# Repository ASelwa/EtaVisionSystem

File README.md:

**EtaVisionSystem**
===============

This repo contains code and documentation for AeroVelo's Eta speedbike vision system.

It includes code for the Arduino Mega, code for the minimOSD, and some documentation as well as datasheets.

####BRANCHES

The _master_ branch contains the most recent updates.

The _BM-2014_ branch is a quick way to access the code ran at Battle Mountain in September 2014. There were several bugs and issues to be addressed, however it still used at road testing several times leading up to 2015.

The _No-Serial-Printing_ branch contains the code ran at Battle Mountain 2014 without serial printing.

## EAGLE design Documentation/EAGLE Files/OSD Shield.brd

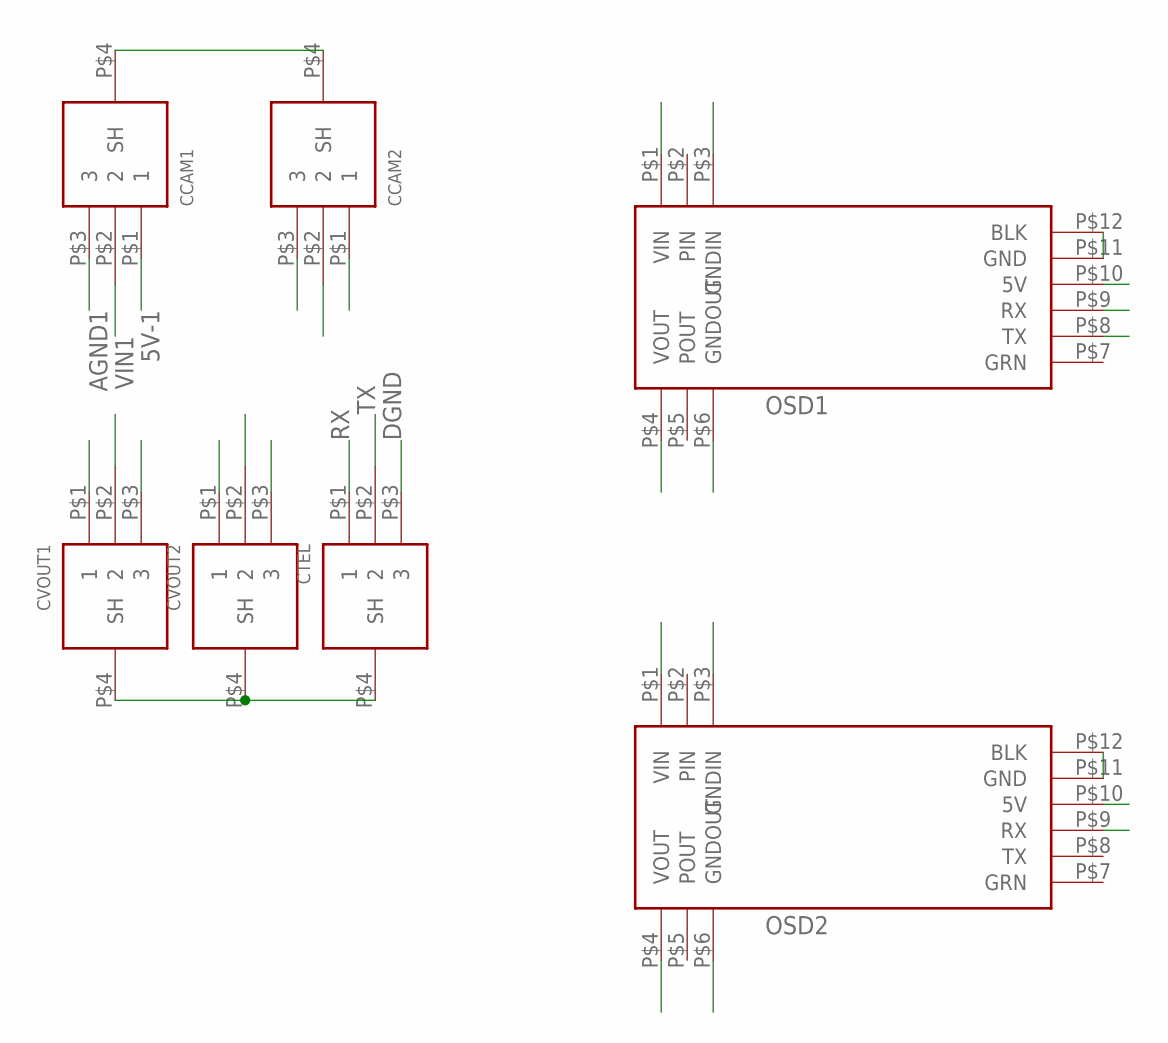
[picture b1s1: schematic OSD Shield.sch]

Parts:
CCAM1, CCAM2: TRA3M
CTEL: TRA3MBARE; TRA3M-BARE
CVOUT1, CVOUT2: TRA3MBARE; TRA3M-BARE
OSD1, OSD2: MINIM-OSD

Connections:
5V-1: CCAM1.P$1 (1), CVOUT1.P$1 (1), OSD1.P$10 (5V)
5V-2: CCAM2.P$1 (1), CVOUT2.P$1 (1), OSD2.P$10 (5V)
AGND1: CCAM1.P$3 (3), CVOUT1.P$3 (3), OSD1.P$3 (GNDIN), OSD1.P$6 (GNDOUT)
AGND2: CCAM2.P$3 (3), CVOUT2.P$3 (3), OSD2.P$3 (GNDIN), OSD2.P$6 (GNDOUT)
DGND: CTEL.P$3 (3), OSD1.P$11 (GND), OSD1.P$12 (BLK), OSD2.P$11 (GND), OSD2.P$12 (BLK)
RX: CTEL.P$1 (1), OSD1.P$9 (RX), OSD2.P$9 (RX)
SHLD: CCAM1.P$4 (SH), CCAM2.P$4 (SH), CTEL.P$4 (SH), CVOUT1.P$4 (SH), CVOUT2.P$4 (SH)
TX: CTEL.P$2 (2), OSD1.P$8 (TX)
VIN1: CCAM1.P$2 (2), OSD1.P$1 (VIN)
VIN2: CCAM2.P$2 (2), OSD2.P$1 (VIN)
VOUT1: CVOUT1.P$2 (2), OSD1.P$4 (VOUT)
VOUT2: CVOUT2.P$2 (2), OSD2.P$4 (VOUT)

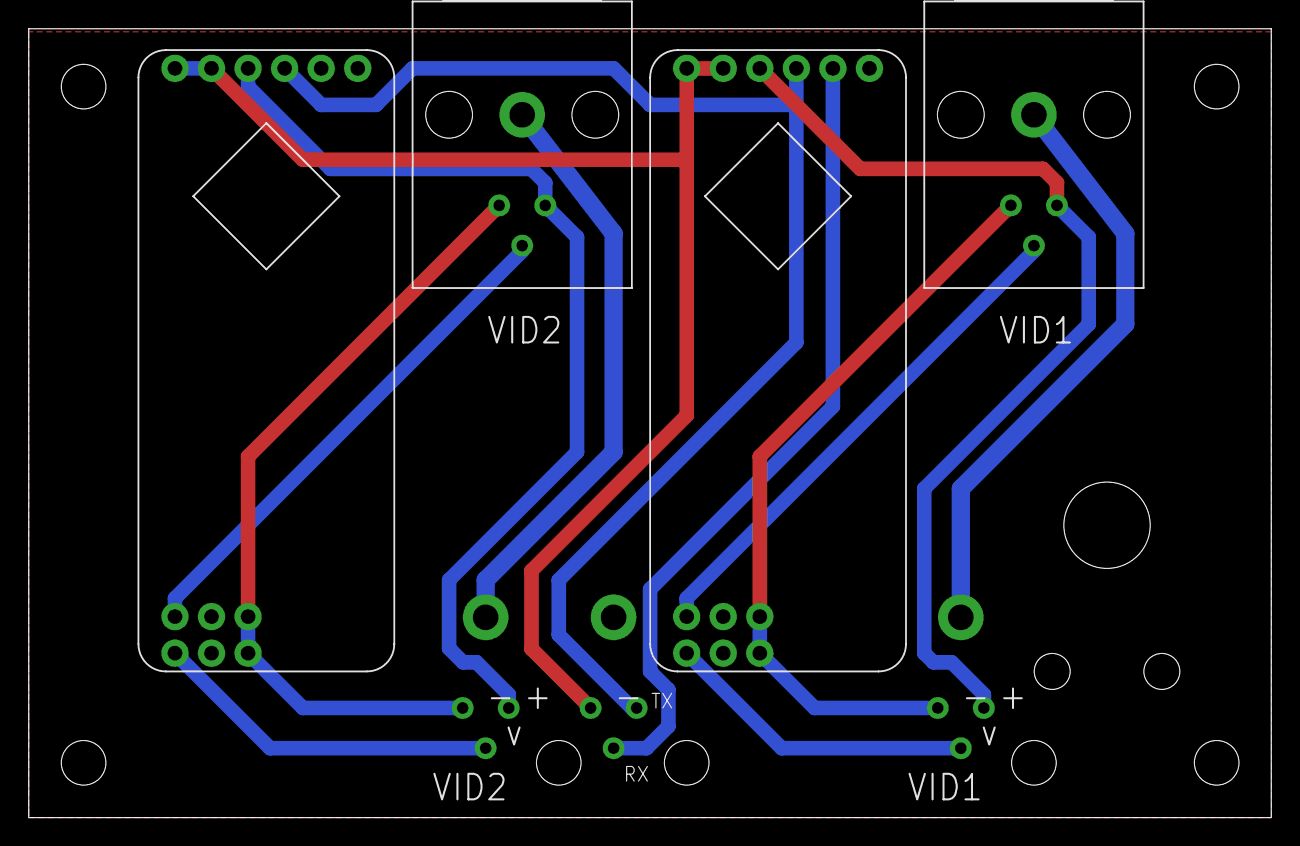
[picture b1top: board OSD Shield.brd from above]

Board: 2 copper layers, 86.3 x 54.8 mm, 7 parts (0 on the bottom side), 12 nets.

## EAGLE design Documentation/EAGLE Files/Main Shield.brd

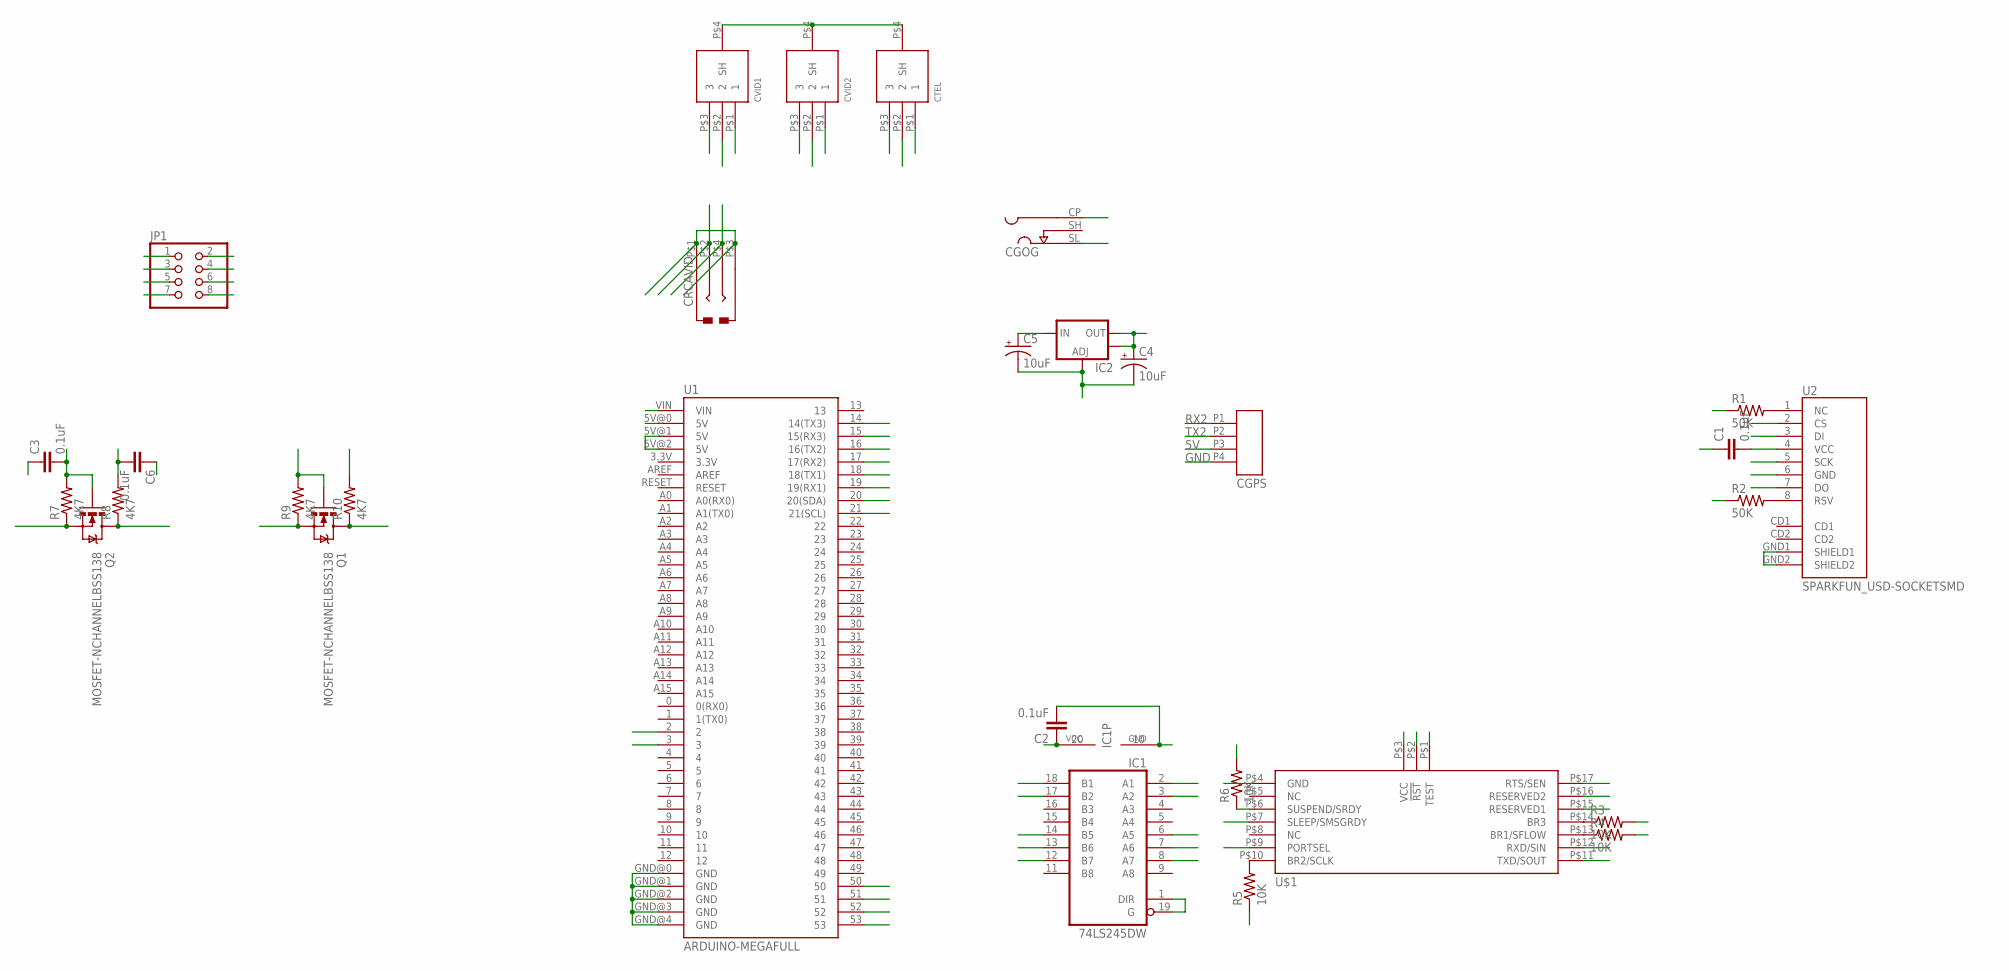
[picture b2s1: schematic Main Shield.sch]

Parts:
C1, C2, C3, C6: 0.1uF; 0603-CAP
C4, C5: 10uF; EIA3216
CGOG: L722RAS
CGPS: TRAPC4MSX
CRCAVID: RCJ-2123
CTEL: TRA3M
CVID1, CVID2: TRA3M
IC1: 74LS245DW; SO20W
IC2: V_REG_LM1117SOT223; SOT223
JP1: PINHD-2X04_MICROMATCH; MICROMATCH-8
Q1, Q2: MOSFET-NCHANNELBSS138; SOT23
R1, R2: 50K; 0603-RES
R3, R4, R5, R6: 10K; 0603-RES
R7, R8, R9, R10: 4K7; 0603-RES
U1: ARDUINO-MEGAFULL; ARDUINO_MEGA
U2: SPARKFUN_USD-SOCKETSMD; SPARKFUN_MICRO-SD-SOCKET-PP
U$1: ANTAP281MXIB

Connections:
3V3: C1.2, C2.1, C3.2, C4.A (+), IC1.20 (VCC), IC2.2 (OUT), IC2.4 (OUT), JP1.2, Q1.1 (G), Q2.1 (G), R1.1, R2.1, R3.2, R4.2, R5.1, R6.2, R7.2, R9.2, U2.4 (VCC), U$1.P$3 (VCC)
5V: C5.A (+), C6.2, CGPS.P3, CVID1.P$1 (1), CVID2.P$1 (1), IC2.3 (IN), JP1.4, R8.2, R10.2, U1.5V@0 (5V), U1.5V@1 (5V), U1.5V@2 (5V)
!RST!ANT: IC1.3 (A2), U$1.P$2 (!RST!)
!RST!ANT5V: IC1.17 (B2), U1.3
CSMMC: IC1.8 (A7), U2.2 (CS)
DIMMC: IC1.7 (A6), U2.3 (DI)
DOMMC: U1.50, U2.7 (DO)
GND: C1.1, C2.2, C3.1, C4.C (-), C5.C (-), C6.1, CGOG.SL (SLEEVE), CGPS.P4, CRCAVID.P$1, CRCAVID.P$3, CTEL.P$3 (3), CTEL.P$4 (SH), CVID1.P$3 (3), CVID1.P$4 (SH), CVID2.P$3 (3), CVID2.P$4 (SH), IC1.1 (DIR), IC1.10 (GND), IC1.19 (G), IC2.1 (ADJ), JP1.1, JP1.3, U1.GND@0 (GND), U1.GND@1 (GND), U1.GND@2 (GND), U1.GND@3 (GND), U1.GND@4 (GND), U2.6 (GND), U2.GND1 (SHIELD1), U2.GND2 (SHIELD2), U$1.P$1 (TEST), U$1.P$4 (GND), U$1.P$7 (SLEEP/SMSGRDY), U$1.P$9 (PORTSEL), U$1.P$15 (RESERVED1), U$1.P$16 (RESERVED2)
MOSI: IC1.13 (B6), U1.51
unnamed: R1.2, U2.1 (NC)
unnamed: R2.2, U2.8 (RSV)
unnamed: R3.1, U$1.P$14 (BR3)
unnamed: R4.1, U$1.P$13 (BR1/SFLOW)
unnamed: R5.2, U$1.P$10 (BR2/SCLK)
unnamed: R6.1, U$1.P$6 (SUSPEND/SRDY)
RTSANT: U1.2, U$1.P$17 (RTS/SEN)
RX2: CGPS.P1, U1.17 (17(RX2))
RXANT: IC1.2 (A1), U$1.P$12 (RXD/SIN)
RXOSD: CTEL.P$2 (2), U1.14 (14(TX3))
SCK: IC1.14 (B5), U1.52
SCKMMC: IC1.6 (A5), U2.5 (SCK)
SCL3V3: JP1.7, Q1.2 (S), R9.1
SCL5V: JP1.8, Q1.3 (D), R10.1, U1.21 (21(SCL))
SDA3V3: JP1.5, Q2.2 (S), R7.1
SDA5V: JP1.6, Q2.3 (D), R8.1, U1.20 (20(SDA))
SS: IC1.12 (B7), U1.53
TX1: IC1.18 (B1), U1.18 (18(TX1))
TX2: CGPS.P2, U1.16 (16(TX2))
TXANT: U1.19 (19(RX1)), U$1.P$11 (TXD/SOUT)
TXOSD: CTEL.P$1 (1), U1.15 (15(RX3))
VBAT: CGOG.CP (CENTRE), U1.VIN
VID1: CRCAVID.P$2, CVID1.P$2 (2)
VID2: CRCAVID.P$4, CVID2.P$2 (2)

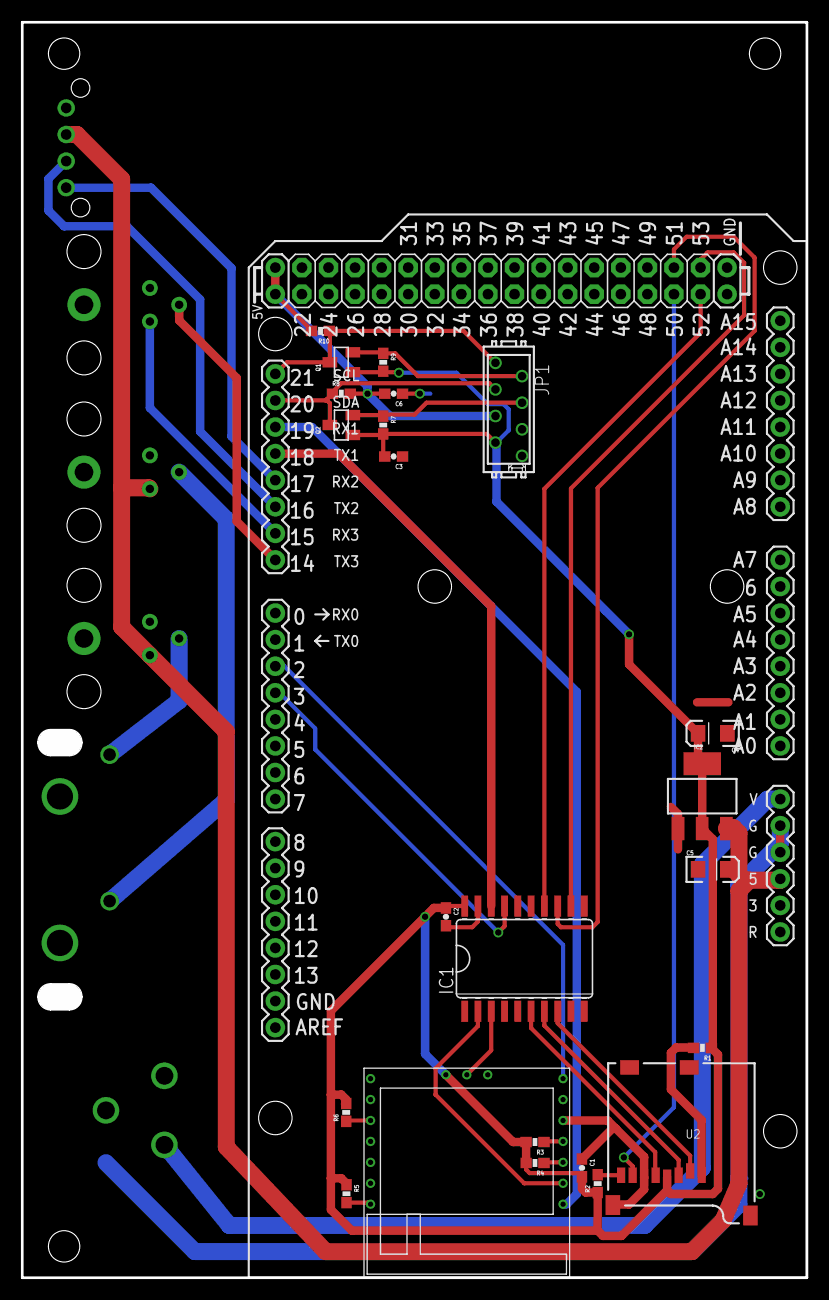
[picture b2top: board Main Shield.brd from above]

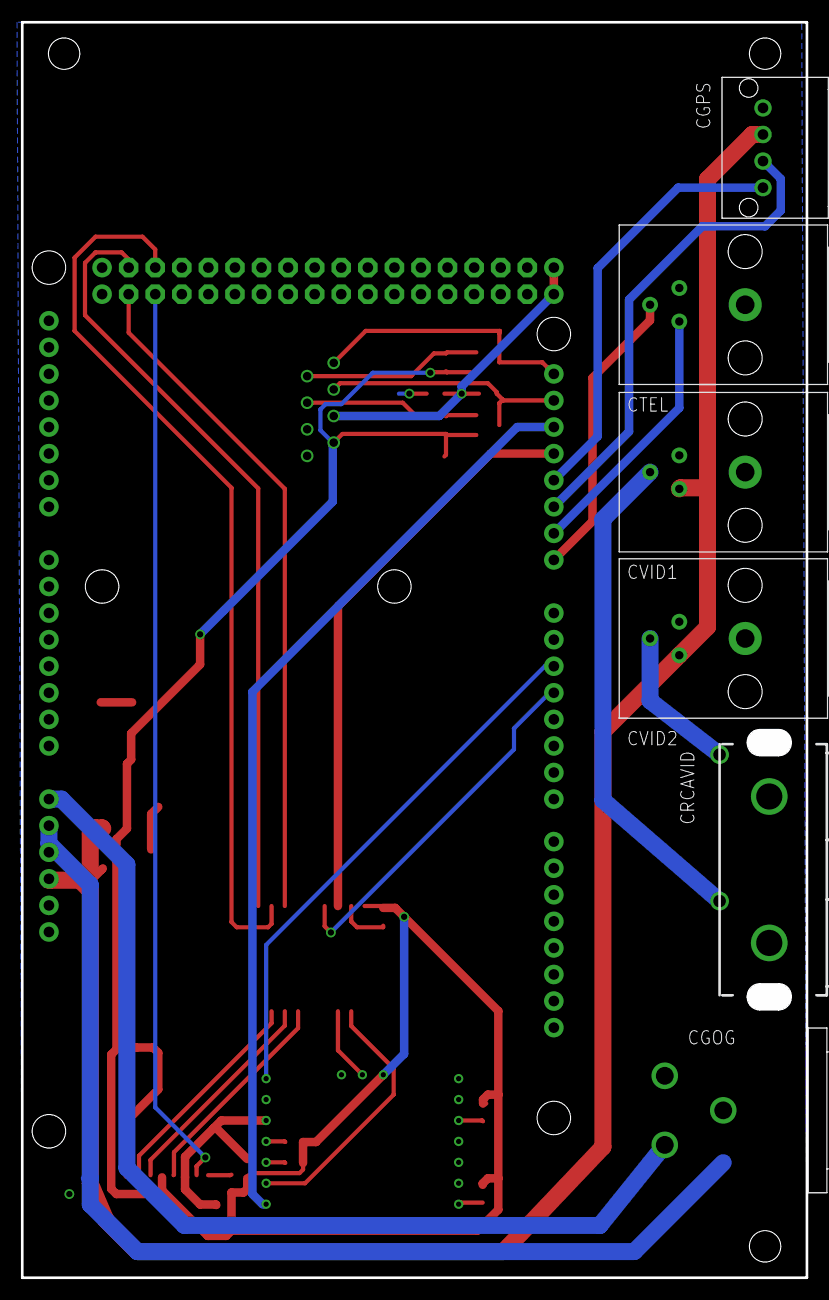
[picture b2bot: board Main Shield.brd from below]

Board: 2 copper layers, 75.0 x 120.0 mm, 30 parts (6 on the bottom side), 33 nets.

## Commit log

2014-07-16 Inital commit - add all the files
2014-07-16 working on elevation power calculations
    working on elevation power calculations
2014-07-16 Replaced ANT_interface2
2014-07-16 Revert "Replaced ANT_interface2"
    This reverts commit 952588fa785ceab49986b3ebbc41c79809ae3066.
2014-07-16 Updated files in HPV_ArduinoMega and HPV_OSD
2014-07-16 Forgot to change test loop back to original loop
2014-07-16 file does not work
    attempted to fix the Pelev calculations but positive feedback screws up
    whole calculation
2014-07-18 changed Pelev
    attempted to correct Pelev calculations, untested
2014-07-18 library for simulation
    moved functions from ANT_interface2 to simulation library
2014-07-18 Integrated code from the ANT interface with OSD and ArduinoMega code
2014-07-23 Added some print statements to test the GPS
2014-07-23 Minor changes to UBLOX and HPV_ArduinoMega for debugging: mostly print statements
2014-07-25 OSD now displays distance travelled based on GPS measurements. No filtering applied. Currently set up to NOT use SD card info.
2014-07-28 Added moving average of last 3 data points
2014-07-28 Added help file for how to display things on the OSD
2014-07-28 Enabled GPS panel
2014-07-29 Heart meter now outputting
2014-07-30 gps test data
    drove from east mall and valhalla inn road to UTM
2014-07-30 Revert "Heart meter now outputting"
    This reverts commit dd00149cfb93f6b963a563ea873c792e10c9e075.
2014-07-30 Revert "Revert "Heart meter now outputting""
    This reverts commit 8f9f0e41a259e8cc47af1755d671c3c69bd85e2c.
2014-07-30 fixed ANT+ for power meter and heart meter
    blah
2014-07-30 Power updates properly on the OSD now, but power calculation is invalid coming out of a coast (not sure if this error was recently introduced or not)
2014-07-31 added simulation mode external variable
    for detecting if rider wants simulation mode
2014-07-31 fixed displaying of variables
2014-07-31 OSD panels are now all functional, added in partial funcionality for simulation mode
2014-07-31 No major changes since last commit. Note that the program is set on simulation mode right now (changed the boolean value in the declaration)
2014-08-04 Disabled first calculation after coming out of a coast: the program no longer shows a spike in velocity, power, distance, etc. Also fixed the distance display to output in metres (not km)
2014-08-04 Realized that simulation was not working: velocity peaked out at 30km/h. Changed algorithm back to non-iterative approach and it worked fine
2014-08-04 Added calibration at the beginning of the program and a new panel for it on the display. Not yet tested.
2014-08-06 Fixed some ANT buffer overflow things and changed the simulation back to iterative (max 2 iterations)
2014-08-06 added powercalc file
    to compare parameters
2014-08-10 Added battery voltage display to OSD and fixed the simulation to run properly with multiple iterations. Target speed isn't quite right yet.
2014-08-11 Fixed target speed to work properly
2014-08-11 Forgot to add the battery file
2014-08-11 Changed code to use analog 2 for battery readings. OSD displays GPS transmission warnings when it stops sending data
2014-08-15 Program will now attempt to connect with GPS when it disconnects. Changed the OSD display to match what Todd wanted. SD card reader code properly implemented with file logger that outputs a CSV.
2014-08-15 Properly configured the distance to go variables and fixed an error (geographic coordinates were previously declared as unsigned)
2014-08-18 Changes to logging and OSD panels. After getting pedals back on the bike, simulation was discovered to behave strangely. Old errors are present again, such as velocity spiking to infinity while coast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
2014-08-19 Found the root of the velocity problems (I think). Added a check guard for CdA to see if it becomes NaN, which should stop the error.
2014-08-19 Added more error-checking in simulate for invalid values. Added support for poewr only messages to be compatible with Vector (untested).
2014-08-22 Changed some logging things and the battery pin.
2014-08-25 temperature testing
    added code for temperature sensor testing, use function readTemp()
2014-08-25 update temperature testing
    added comments, removed function input variable
2014-08-25 Minor changes to logging
2014-08-25 added pwrAvg and tenSecPower functions
    to be displayed on screen
2014-08-25 Added OSD support for 10s moving power average and target poewr
2014-08-25 Added in target power and average power displays
2014-08-26 Minor fixes to power averaging behaviour: fixed division by zero in pwrAvg and made program skip averaging if power is 0W (otherwise it starts averaging as soon as you switch profiles)
2014-08-27 Changes to pins used for measuring values. Also changed the baud rate for the antenna back to what it really was and should have been
2014-08-27 Added temperature warning to OSD and started implementing battery warning
2014-08-27 Finished implementing battery and temperature OSD. Both use artificial thresholds.
2014-08-27 Corrected the battery and temperature displays. Added some documentation to the repository.
2014-08-27 Added temp_sense.ino back in. No change.
2014-09-01 Changed some pins to their correct new locations.
2014-09-01 Cleaned up all the code to get rid of useless commented stuff. Also implemented power target for real-time mode and fixed OSD text on profiles so it wouldn't cut into the low battery warning. Everyth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
2014-09-03 Removed misleading and unused preprocessor variable and added documentation file
2014-09-03 Added PDF version of documentation
2014-09-06 Corrected inconsistency with the type of "displacement" when it is sent in the slip buffer (signed vs. unsigned)
2014-09-06 Changed OSD to not display GPS transmission information
2014-09-07 Fixed two inconsistencies with the type of variable "displacement"
2014-09-07 Changed the time to wait before resetting the GPS if the connection is lost
2014-09-07 The "unit" conversion doesn't work after the cos
    Dividing by 10000 needs to be done before cosine is applied since it
    isn’t a linear function
2014-09-09 GPS math fix and calibrate enabled
2014-09-10 Added support for an additional log file that writes whenever new power messages are received.
2014-09-10 Edit screen layout
2014-09-10 (char *) needed for sd_print (not sure if proper)
2014-09-14 Commented Serial Prints
2014-09-27 Organize files a bit
2014-09-27 Added Log files from BM2014
2014-09-28 File Management
2014-09-29 More File Rearranging
2014-10-06 Added some information to the documentation.
2015-05-28 Added AP_Math Library
2015-05-28 Revert "Added AP_Math Library"
    This reverts commit 6aad5b69f4ba445e98ec9297cde0ac1f6e344759.
2015-05-28 Added AP_Math Library (correctly)
2015-08-17 Update README
    See the README for an explanation of this branch, and all other
    branches in existence at the present time.
2015-08-17 Update README to explain branch organization
2015-08-17 Update README to explain current branches
2015-08-17 Update documentation to the most recent and complete version
2015-08-18 Added timeout to pedals calibration, and started implementing separate screen at beginning
2015-08-18 Working Road Testing Version
    Includes new calibration, minor fixes, updates, etc. The OSD displays
    displacement from the starting location, which is taken when the unit
    is turned on.
2015-08-23 Added O2CO2 files
2015-08-23 Updated CO2 O2 Temp
2015-08-24 Latest Used Version
    Note the n_average parameters and DATA_SIZE. Also it now requires a
    capacitor over the reset pin to prevent serial monitor reset. (But
    can’t flash with the capacitor connected)
2015-08-24 Some updates for logging including stream down print statements for more data logging
2015-08-25 File Organization and renaming
2015-08-25 Save configuration before changing to loop based on time
2015-08-26 Data Acquisition V2 for OpenLog created
2015-08-26 8am runs @ TRC
2015-08-26 CHECKPOINT: Main system running well at GM and TRC
2015-08-27 CHECKPOINT: OpenLog working
2015-08-27 CHECKPOINT: Evening Runs @TRC, ran pretty smoothly, includes live simulation while riding
2015-08-28 Last code at TRC
2015-08-30 Large Changes, organizing flow and separating more into other files
2015-08-31 Accelerometer and general structure changes
2015-09-01 Working accelerometer and OSD
2015-09-03 Working hall sensor and several other changes
2015-09-05 Simulation fixes and hall effect integration
2015-09-14 Plenty of changes, but working alright just before qualifers
2015-09-17 Fixed target speed profile and power profile, braking bar updated
    (SD card problem gone, and speed profile gone)
2015-09-17 (remove debugging lines from previous commit)
2015-09-18 Save before adjusting OSD and power profiles

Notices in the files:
parts and their libraries:
SparkFun-Capacitors: Licensing: CC v3.0 Share-Alike You are welcome to use this library for commercial purposes.
